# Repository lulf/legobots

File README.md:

# legobots

Repository with various firmware and software for lego-related projects:

* Lego engine controller
* Lego sorter firmware
* Lego brick classifier
* BLE remote for lego engine

The stuff is mostly in a half-working state.

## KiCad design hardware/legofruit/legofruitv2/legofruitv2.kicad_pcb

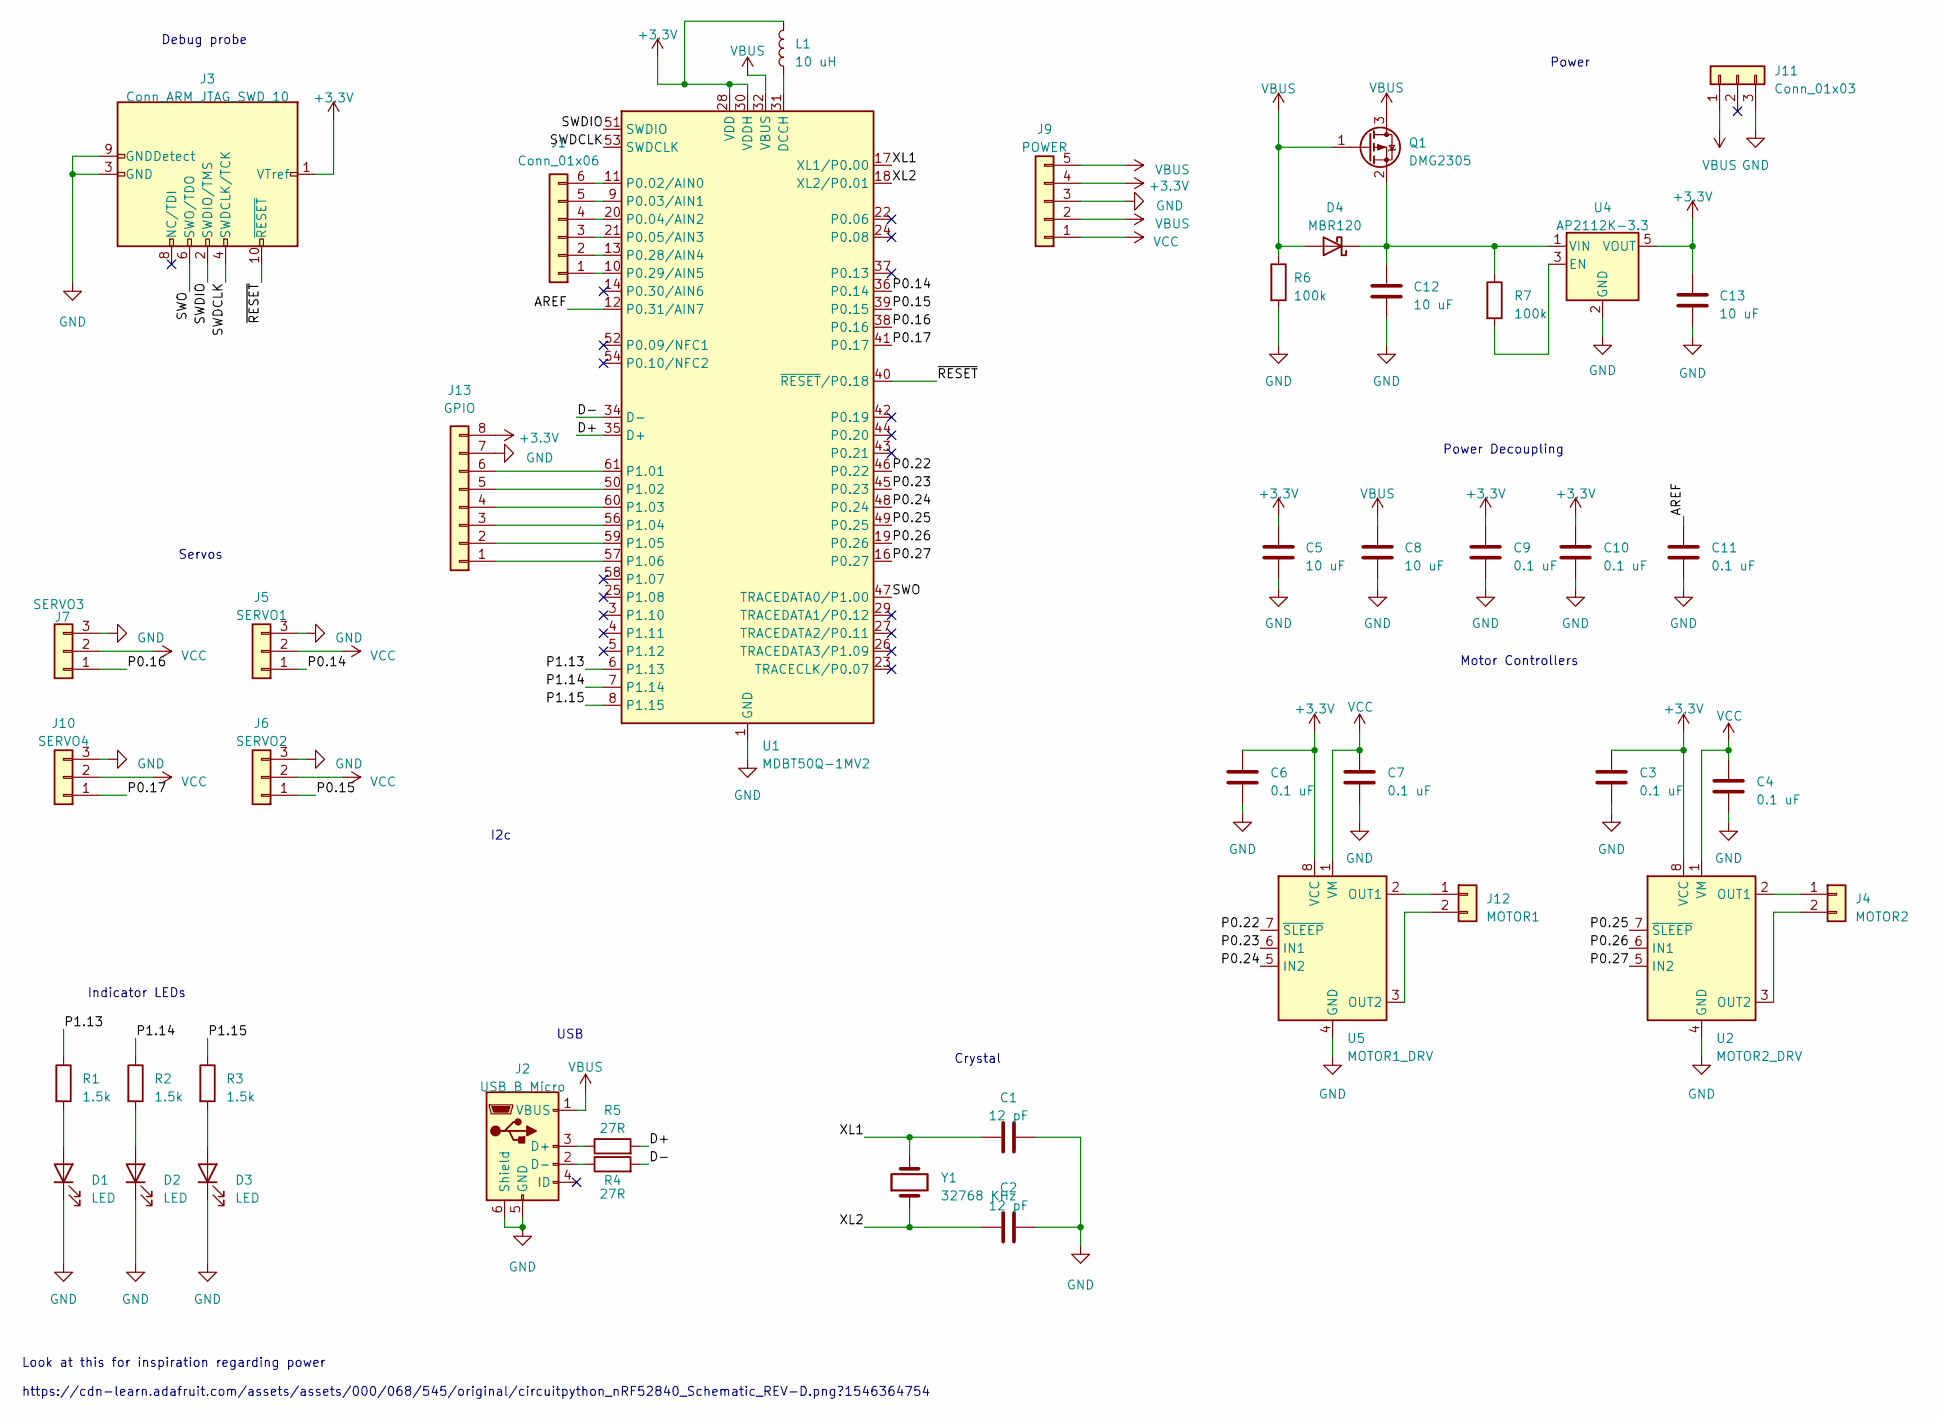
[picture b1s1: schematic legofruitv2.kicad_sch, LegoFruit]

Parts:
C1, C2: 12 pF; C_0805_2012Metric_Pad1.18x1.45mm_HandSolder; MPN CHV0805N250120FCT; Digi-Key_PN 4713-CHV0805N250120FCT-ND
C3, C4, C6, C7, C9, C10, C11: 0.1 uF; C_0805_2012Metric_Pad1.18x1.45mm_HandSolder; MPN CL21B104KBCNNNC; Digi-Key_PN 1276-1003-2-ND
C5, C8, C12, C13: 10 uF; C_0805_2012Metric_Pad1.18x1.45mm_HandSolder; MPN CL21A106KAYNNNE; Digi-Key_PN 1276-2891-2-ND
D1, D2, D3: LED; LED_0805_2012Metric_Pad1.15x1.40mm_HandSolder
D4: MBR120; D_SOD-123F; Digi-Key_PN MBR120LSFT1GOSCT-ND
J1: Conn_01x06; PinHeader_1x05_P2.54mm_Vertical
J2: USB_B_Micro; USB_Micro-AB_Molex_47590-0001
J3: Conn_ARM_JTAG_SWD_10; PinHeader_2x05_P1.27mm_Vertical_SMD; MPN 3220-10-0300-00; Digi-Key_PN 1175-1629-ND
J4: MOTOR2; PinHeader_1x02_P2.54mm_Vertical
J5: SERVO1; PinHeader_1x03_P2.54mm_Vertical
J6: SERVO2; PinHeader_1x03_P2.54mm_Vertical
J7: SERVO3; PinHeader_1x03_P2.54mm_Vertical
J9: POWER; PinHeader_1x05_P2.54mm_Vertical
J10: SERVO4; PinHeader_1x03_P2.54mm_Vertical
J11: Conn_01x03; JST_GH_BM03B-GHS-TBT_1x03-1MP_P1.25mm_Vertical; MPN BM03B-GHS-TBT; Digi-Key_PN 455-BM03B-GHS-TBTCT-ND
J12: MOTOR1; PinHeader_1x02_P2.54mm_Vertical
J13: GPIO; PinHeader_1x08_P2.54mm_Vertical
L1: 10 uH; L_0603_1608Metric_Pad1.05x0.95mm_HandSolder; MPN LQM18FN100M00D; Digi-Key_PN 490-4025-1-ND
Q1: DMG2305; SOT-23; MPN DMG2305UX-13; Digi-Key_PN DMG2305UX-13DICT-ND
R1, R2, R3: 1.5k; R_0805_2012Metric_Pad1.20x1.40mm_HandSolder
R4, R5: 27R; R_0805_2012Metric_Pad1.20x1.40mm_HandSolder
R6, R7: 100k; R_0805_2012Metric_Pad1.20x1.40mm_HandSolder
U1: MDBT50Q-1MV2; Raytac_MDBT50Q; Digi-Key_PN 3271-MDBT50Q-1MV2-ND
U2: MOTOR2_DRV; WSON-8-1EP_2x2mm_P0.5mm_EP0.9x1.6mm; MPN DRV8837DSGR; Digi-Key_PN 296-34806-1-ND
U4: AP2112K-3.3; SOT-23-5; MPN AP2112K-3.3TRG1; Digi-Key_PN AP2112K-3.3TRG1DICT-ND
U5: MOTOR1_DRV; WSON-8-1EP_2x2mm_P0.5mm_EP0.9x1.6mm; MPN DRV8837DSGR; Digi-Key_PN 296-34806-1-ND
Y1: 32768 KHz; Crystal_SMD_MicroCrystal_CC7V-T1A-2Pin_3.2x1.5mm_HandSolder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; MPN ABS07-32.768KHZ-T; Digi-Key_PN 535-9542-1-ND

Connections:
+3.3V: C3.1, C5.1, C6.1, C9.1, C10.1, C13.1, J3.1 (VTref), J9.4, J13.8, L1.2, U1.28 (VDD), U1.30 (VDDH), U2.8 (VCC), U4.5 (VOUT), U5.8 (VCC)
/AREF: C11.1, U1.12 (P0.31/AIN7)
/D+: R5.2, U1.35 (D+)
/D-: R4.2, U1.34 (D-)
/P0.14: J5.1, U1.36 (P0.14)
/P0.15: J6.1, U1.39 (P0.15)
/P0.16: J7.1, U1.38 (P0.16)
/P0.17: J10.1, U1.41 (P0.17)
/P0.22: U1.46 (P0.22), U5.7 (~SLEEP)
/P0.23: U1.45 (P0.23), U5.6 (IN1)
/P0.24: U1.48 (P0.24), U5.5 (IN2)
/P0.25: U1.49 (P0.25), U2.7 (~SLEEP)
/P0.26: U1.19 (P0.26), U2.6 (IN1)
/P0.27: U1.16 (P0.27), U2.5 (IN2)
/P1.13: R1.1, U1.6 (P1.13)
/P1.14: R2.1, U1.7 (P1.14)
/P1.15: R3.1, U1.8 (P1.15)
/SWDCLK: J3.4 (SWDCLK/TCK), U1.53 (SWDCLK)
/SWDIO: J3.2 (SWDIO/TMS), U1.51 (SWDIO)
/SWO: J3.6 (SWO/TDO), U1.47 (TRACEDATA0/P1.00)
/XL1: C1.1, U1.17 (XL1/P0.00), Y1.2
/XL2: C2.1, U1.18 (XL2/P0.01), Y1.1
/~RESET: J3.10 (~RESET), U1.40 (~RESET/P0.18)
GND: C1.2, C2.2, C3.2, C4.2, C5.2, C6.2, C7.2, C8.2, C9.2, C10.2, C11.2, C12.2, C13.2, D1.1 (K), D2.1 (K), D3.1 (K), J2.5 (GND), J2.6 (Shield), J3.3 (GND), J3.5 (GND), J3.9 (GNDDetect), J5.3, J6.3, J7.3, J9.3, J10.3, J11.3, J13.7, R6.2, U1.1 (GND), U1.2 (GND), U1.15 (GND), U1.33 (GND), U1.55 (GND), U2.4 (GND), U2.9 (GND), U4.2 (GND), U5.4 (GND), U5.9 (GND)
unnamed: D1.2 (A), R1.2
unnamed: D2.2 (A), R2.2
unnamed: D3.2 (A), R3.2
unnamed: C12.1, D4.1 (K), Q1.2 (S), R7.1, U4.1 (VIN)
unnamed: J1.1, U1.10 (P0.29/AIN5)
unnamed: J1.2, U1.13 (P0.28/AIN4)
unnamed: J1.3, U1.21 (P0.05/AIN3)
unnamed: J1.4, U1.20 (P0.04/AIN2)
unnamed: J1.5, U1.9 (P0.03/AIN1)
unnamed: J1.6, U1.11 (P0.02/AIN0)
unnamed: J2.3 (D+), R5.1
unnamed: J2.2 (D-), R4.1
unnamed: J4.1, U2.2 (OUT1)
unnamed: J4.2, U2.3 (OUT2)
unnamed: J12.1, U5.2 (OUT1)
unnamed: J12.2, U5.3 (OUT2)
unnamed: J13.1, U1.57 (P1.06)
unnamed: J13.2, U1.59 (P1.05)
unnamed: J13.3, U1.56 (P1.04)
unnamed: J13.4, U1.60 (P1.03)
unnamed: J13.5, U1.50 (P1.02)
unnamed: J13.6, U1.61 (P1.01)
unnamed: L1.1, U1.31 (DCCH)
unnamed: R7.2, U4.3 (EN)
VBUS: C8.1, D4.2 (A), J2.1 (VBUS), J9.2, J9.5, J11.1, Q1.1 (G), Q1.3 (D), R6.1, U1.32 (VBUS)
VCC: C4.1, C7.1, J5.2, J6.2, J7.2, J9.1, J10.2, U2.1 (VM), U5.1 (VM)

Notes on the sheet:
Power Decoupling
I2c
Debug probe
Crystal
Servos
Indicator LEDs
Look at this for inspiration regarding power https://cdn-learn.adafruit.com/assets/assets/000/068/545/original/circuitpython_nRF52840_Schematic_REV-D.png?1546364754
Motor Controllers
Power
USB

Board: 2 copper layers, 47 parts (0 on the bottom side), 49 nets, no tracks yet.

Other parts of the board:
MH: brick-1x1
MH#2, MH#3, MH#4: brick-1x1

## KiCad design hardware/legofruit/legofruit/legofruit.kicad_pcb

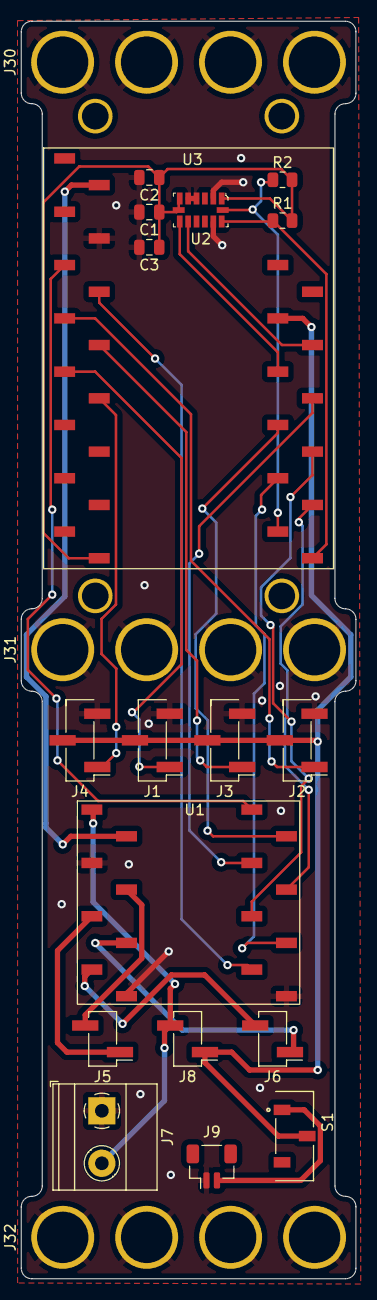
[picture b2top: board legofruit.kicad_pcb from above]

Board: 2 copper layers, 31.9 x 119.8 mm, 21 parts (0 on the bottom side), 25 nets.

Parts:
C1: 10u; C_0805_2012Metric
C2, C3: 100n; C_0805_2012Metric
J1: SERVO_3; PinHeader_1x03_P2.54mm_Vertical_SMD_Pin1Left
J2: SERVO_1; PinHeader_1x03_P2.54mm_Vertical_SMD_Pin1Left
J3: SERVO_2; PinHeader_1x03_P2.54mm_Vertical_SMD_Pin1Left
J4: SERVO_4; PinHeader_1x03_P2.54mm_Vertical_SMD_Pin1Left
J5: MOTOR1; PinHeader_1x02_P2.54mm_Vertical_SMD_Pin1Left
J6: MOTOR2; PinHeader_1x02_P2.54mm_Vertical_SMD_Pin1Left
J7: Screw_Terminal_01x02; TerminalBlock_Phoenix_MKDS-1,5-2_1x02_P5.00mm_Horizontal
J8: MOTOR_USB; PinHeader_1x02_P2.54mm_Vertical_SMD_Pin1Left
J9: JST_POWER; JST_SH_BM02B-SRSS-TB_1x02-1MP_P1.00mm_Vertical
J30, J31, J32: Conn_01x04; brick-1x4
R1, R2: 10k; R_0805_2012Metric
S1: JS102011JCQN; SW_JS102011JCQN
U1: TB6612FNG; sparkfun_motor
U2: ADXL345BCCZ; LGA-14_3x5mm_RevA
U3: feather_nrf52840; feather_header_smd

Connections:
/3V3: U1.20 (VCC), U3.14 (3.3V)
/A0: U1.23 (PWMA), U3.17 (A0)
/A1: U1.15 (PWMB), U3.18 (A1)
/A2: J2.1, U3.19 (A2)
/A3: J3.1, U3.20 (A3)
/A4: J1.1, U3.21 (A4)
/A5: J4.1, U3.22 (A5)
/D2: C1.1, C2.1, C3.1, R1.2, R2.2, U2.1 (VDD_I/O), U2.6 (VS), U2.7 (~CS), U3.28 (D2)
/D5: U1.19 (STBY), U3.10 (D5)
/D6: U1.16 (BIN2), U3.9 (D6)
/D9: U1.17 (BIN1), U3.8 (D9)
/D10: U1.22 (AIN2), U3.7 (D10)
/D11: U1.21 (AIN1), U3.6 (D11)
/D12: U2.8 (INT1), U3.5 (D12)
/D13: U2.9 (INT2), U3.4 (D13)
/SCL: R2.1, U2.14 (SCL/SCLK), U3.11 (SCL)
/SDA: R1.1, U2.13 (SDA/SDI/SDIO), U3.12 (SDA)
/USB: J1.2, J2.2, J3.2, J4.2, J8.1, S1.2, U3.3 (USB)
GND: C1.2, C2.2, C3.2, J1.3, J2.3, J3.3, J4.3, J7.1, J9.1, J30.1, J30.2, J30.3, J30.4, J31.1, J31.2, J31.3, J31.4, J32.1, J32.2, J32.3, J32.4, U1.3 (PGND1), U1.9 (PGND2), U1.18 (GND), U2.2 (GND), U2.4 (GND), U2.5 (GND), U2.12 (SDO/ALT_ADD), U3.16 (GND)
unnamed: J5.1, U1.5 (AO2)
unnamed: J5.2, U1.1 (AO1)
unnamed: J6.1, U1.7 (BO2)
unnamed: J6.2, U1.11 (BO1)
unnamed: J9.2, S1.1
VDD: J7.2, J8.2, U1.24 (VM1)

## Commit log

2022-04-14 Initial classifier work
2022-04-14 Add firmware for controller
2022-04-14 PWM programming
2022-04-15 Rename and move
2022-04-15 Add button control
2022-04-15 Refactor
2022-05-06 Import trainbot
2022-05-06 Add trainbot remote
2022-05-06 Fully working remote
2022-05-07 More robust handling
2022-05-20 Add legofruit board
2022-05-20 Fixes
2022-07-21 Fixup
2022-07-22 Initial new sortbot
2022-07-22 Add compiler config
2022-09-04 Test pwm
2022-09-16 Add opencv-based classifier
2022-10-12 Add readme
2022-12-21 add missing servo
2023-01-09 move
2023-01-09 move bootloader
2023-02-12 move trainbot
2023-02-12 initial version of beltbot firmware
2023-02-12 fix: upgrade embassy version
2023-02-12 support two motors
2023-02-12 add beltbot remote
2023-02-12 Bump tokio from 1.20.0 to 1.20.4 in /sortbot
    Bumps [tokio](https://github.com/tokio-rs/tokio) from 1.20.0 to 1.20.4.
    - [Release notes](https://github.com/tokio-rs/tokio/releases)
    - [Commits](https://github.com/tokio-rs/tokio/compare/tokio-1.20.0...tokio-1.20.4)
    ---
    updated-dependencies:
    - dependency-name: tokio
2024-02-06 finish beltbot work
2024-02-07 add carbot
2024-02-07 implement servo and motor control
2024-02-07 add missing files
2024-02-07 configure device
2024-02-08 add remote android app
2024-02-08 tuning
2024-07-22 add v2 legofruit
2024-12-28 Update sortbot to new sensor
2024-12-28 Device driver version
